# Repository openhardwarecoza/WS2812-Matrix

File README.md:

# WS2812-Matrix
LED Matrix Panels

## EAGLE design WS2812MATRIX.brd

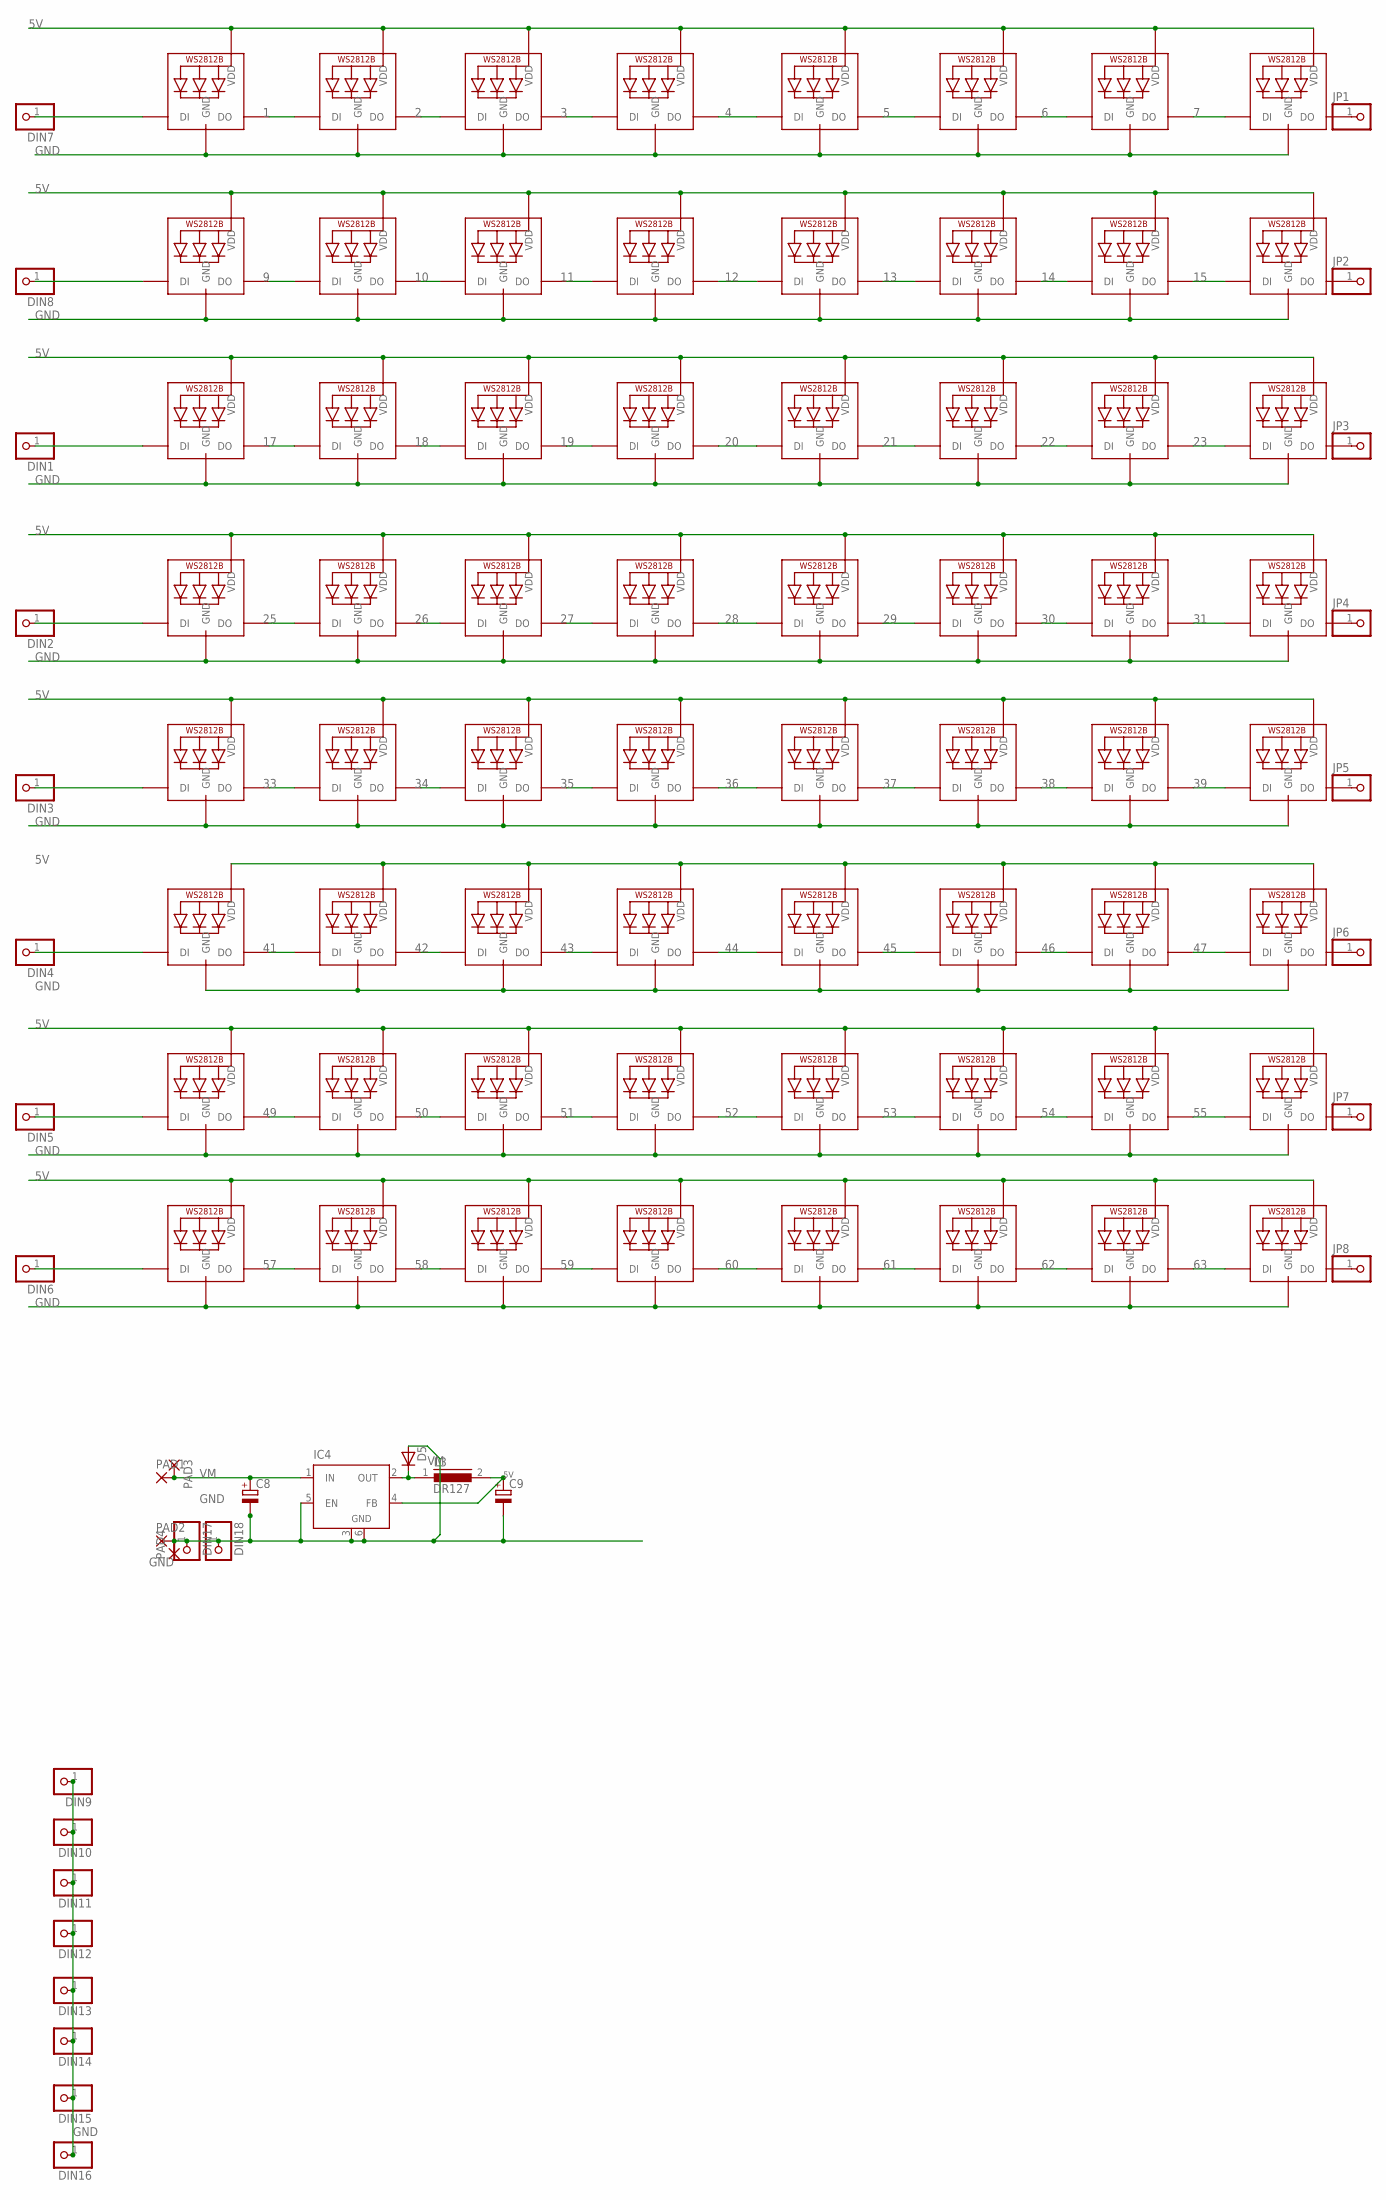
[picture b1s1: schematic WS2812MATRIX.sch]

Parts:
C8, C9: CPOL-EUE3.5-10; E3,5-10
D5: D-SOD-87; SOD87
DIN1, DIN2, DIN3, DIN4, DIN5, DIN6, DIN7, DIN8, DIN9, DIN10, DIN11, DIN12, DIN13, DIN14, DIN15, DIN16, DIN17, DIN18: PINHD-1X1; 1X01
IC4: LM2596S; TO263-5
JP1, JP2, JP3, JP4, JP5, JP6, JP7, JP8: PINHD-1X1; 1X01
L3: DR127
LED1, LED2, LED3, LED4, LED5, LED6, LED7, LED8, LED9, LED10, LED11, LED12, LED13, LED14, LED15, LED16, LED17, LED18, LED19, LED20, LED21, LED22, LED23, LED24, LED25, LED26, LED27, LED28, LED29, LED30, LED31, LED32, LED33, LED34, LED35, LED36, LED37, LED38, LED39, LED40, LED41, LED42, LED43, LED44, LED45, LED46, LED47, LED48, LED49, LED50, LED51, LED52, LED53, LED54, LED55, LED56, LED57, LED58, LED59, LED60, LED61, LED62, LED63, LED64: WS2812B5050; WS2812B
PAD1, PAD2, PAD3, PAD4: 2,54/1,1

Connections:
1: LED9.2-DOUT (DO), LED10.4-DIN (DI)
2: LED10.2-DOUT (DO), LED11.4-DIN (DI)
3: LED11.2-DOUT (DO), LED12.4-DIN (DI)
4: LED12.2-DOUT (DO), LED13.4-DIN (DI)
5: LED13.2-DOUT (DO), LED14.4-DIN (DI)
5V: C9.+, IC4.4 (FB), L3.2, LED1.1-VDD (VDD), LED2.1-VDD (VDD), LED3.1-VDD (VDD), LED4.1-VDD (VDD), LED5.1-VDD (VDD), LED6.1-VDD (VDD), LED7.1-VDD (VDD), LED8.1-VDD (VDD), LED9.1-VDD (VDD), LED10.1-VDD (VDD), LED11.1-VDD (VDD), LED12.1-VDD (VDD), LED13.1-VDD (VDD), LED14.1-VDD (VDD), LED15.1-VDD (VDD), LED16.1-VDD (VDD), LED17.1-VDD (VDD), LED18.1-VDD (VDD), LED19.1-VDD (VDD), LED20.1-VDD (VDD), LED21.1-VDD (VDD), LED22.1-VDD (VDD), LED23.1-VDD (VDD), LED24.1-VDD (VDD), LED25.1-VDD (VDD), LED26.1-VDD (VDD), LED27.1-VDD (VDD), LED28.1-VDD (VDD), LED29.1-VDD (VDD), LED30.1-VDD (VDD), LED31.1-VDD (VDD), LED32.1-VDD (VDD), LED33.1-VDD (VDD), LED34.1-VDD (VDD), LED35.1-VDD (VDD), LED36.1-VDD (VDD), LED37.1-VDD (VDD), LED38.1-VDD (VDD), LED39.1-VDD (VDD), LED40.1-VDD (VDD), LED41.1-VDD (VDD), LED42.1-VDD (VDD), LED43.1-VDD (VDD), LED44.1-VDD (VDD), LED45.1-VDD (VDD), LED46.1-VDD (VDD), LED47.1-VDD (VDD), LED48.1-VDD (VDD), LED49.1-VDD (VDD), LED50.1-VDD (VDD), LED51.1-VDD (VDD), LED52.1-VDD (VDD), LED53.1-VDD (VDD), LED54.1-VDD (VDD), LED55.1-VDD (VDD), LED56.1-VDD (VDD), LED57.1-VDD (VDD), LED58.1-VDD (VDD), LED59.1-VDD (VDD), LED60.1-VDD (VDD), LED61.1-VDD (VDD), LED62.1-VDD (VDD), LED63.1-VDD (VDD), LED64.1-VDD (VDD)
6: LED14.2-DOUT (DO), LED15.4-DIN (DI)
7: LED15.2-DOUT (DO), LED16.4-DIN (DI)
9: LED1.2-DOUT (DO), LED2.4-DIN (DI)
10: LED2.2-DOUT (DO), LED3.4-DIN (DI)
11: LED3.2-DOUT (DO), LED4.4-DIN (DI)
12: LED4.2-DOUT (DO), LED5.4-DIN (DI)
13: LED5.2-DOUT (DO), LED6.4-DIN (DI)
14: LED6.2-DOUT (DO), LED7.4-DIN (DI)
15: LED7.2-DOUT (DO), LED8.4-DIN (DI)
17: LED17.2-DOUT (DO), LED18.4-DIN (DI)
18: LED18.2-DOUT (DO), LED19.4-DIN (DI)
19: LED19.2-DOUT (DO), LED20.4-DIN (DI)
20: LED20.2-DOUT (DO), LED21.4-DIN (DI)
21: LED21.2-DOUT (DO), LED22.4-DIN (DI)
22: LED22.2-DOUT (DO), LED23.4-DIN (DI)
23: LED23.2-DOUT (DO), LED24.4-DIN (DI)
25: LED25.2-DOUT (DO), LED26.4-DIN (DI)
26: LED26.2-DOUT (DO), LED27.4-DIN (DI)
27: LED27.2-DOUT (DO), LED28.4-DIN (DI)
28: LED28.2-DOUT (DO), LED29.4-DIN (DI)
29: LED29.2-DOUT (DO), LED30.4-DIN (DI)
30: LED30.2-DOUT (DO), LED31.4-DIN (DI)
31: LED31.2-DOUT (DO), LED32.4-DIN (DI)
33: LED33.2-DOUT (DO), LED34.4-DIN (DI)
34: LED34.2-DOUT (DO), LED35.4-DIN (DI)
35: LED35.2-DOUT (DO), LED36.4-DIN (DI)
36: LED36.2-DOUT (DO), LED37.4-DIN (DI)
37: LED37.2-DOUT (DO), LED38.4-DIN (DI)
38: LED38.2-DOUT (DO), LED39.4-DIN (DI)
39: LED39.2-DOUT (DO), LED40.4-DIN (DI)
41: LED41.2-DOUT (DO), LED42.4-DIN (DI)
42: LED42.2-DOUT (DO), LED43.4-DIN (DI)
43: LED43.2-DOUT (DO), LED44.4-DIN (DI)
44: LED44.2-DOUT (DO), LED45.4-DIN (DI)
45: LED45.2-DOUT (DO), LED46.4-DIN (DI)
46: LED46.2-DOUT (DO), LED47.4-DIN (DI)
47: LED47.2-DOUT (DO), LED48.4-DIN (DI)
49: LED49.2-DOUT (DO), LED50.4-DIN (DI)
50: LED50.2-DOUT (DO), LED51.4-DIN (DI)
51: LED51.2-DOUT (DO), LED52.4-DIN (DI)
52: LED52.2-DOUT (DO), LED53.4-DIN (DI)
53: LED53.2-DOUT (DO), LED54.4-DIN (DI)
54: LED54.2-DOUT (DO), LED55.4-DIN (DI)
55: LED55.2-DOUT (DO), LED56.4-DIN (DI)
57: LED57.2-DOUT (DO), LED58.4-DIN (DI)
58: LED58.2-DOUT (DO), LED59.4-DIN (DI)
59: LED59.2-DOUT (DO), LED60.4-DIN (DI)
60: LED60.2-DOUT (DO), LED61.4-DIN (DI)
61: LED61.2-DOUT (DO), LED62.4-DIN (DI)
62: LED62.2-DOUT (DO), LED63.4-DIN (DI)
63: LED63.2-DOUT (DO), LED64.4-DIN (DI)
GND: C8.-, C9.-, D5.2 (A), DIN9.1, DIN10.1, DIN11.1, DIN12.1, DIN13.1, DIN14.1, DIN15.1, DIN16.1, DIN17.1, DIN18.1, IC4.3 (GND), IC4.5 (EN), IC4.6 (GND), LED1.3-GND (GND), LED2.3-GND (GND), LED3.3-GND (GND), LED4.3-GND (GND), LED5.3-GND (GND), LED6.3-GND (GND), LED7.3-GND (GND), LED8.3-GND (GND), LED9.3-GND (GND), LED10.3-GND (GND), LED11.3-GND (GND), LED12.3-GND (GND), LED13.3-GND (GND), LED14.3-GND (GND), LED15.3-GND (GND), LED16.3-GND (GND), LED17.3-GND (GND), LED18.3-GND (GND), LED19.3-GND (GND), LED20.3-GND (GND), LED21.3-GND (GND), LED22.3-GND (GND), LED23.3-GND (GND), LED24.3-GND (GND), LED25.3-GND (GND), LED26.3-GND (GND), LED27.3-GND (GND), LED28.3-GND (GND), LED29.3-GND (GND), LED30.3-GND (GND), LED31.3-GND (GND), LED32.3-GND (GND), LED33.3-GND (GND), LED34.3-GND (GND), LED35.3-GND (GND), LED36.3-GND (GND), LED37.3-GND (GND), LED38.3-GND (GND), LED39.3-GND (GND), LED40.3-GND (GND), LED41.3-GND (GND), LED42.3-GND (GND), LED43.3-GND (GND), LED44.3-GND (GND), LED45.3-GND (GND), LED46.3-GND (GND), LED47.3-GND (GND), LED48.3-GND (GND), LED49.3-GND (GND), LED50.3-GND (GND), LED51.3-GND (GND), LED52.3-GND (GND), LED53.3-GND (GND), LED54.3-GND (GND), LED55.3-GND (GND), LED56.3-GND (GND), LED57.3-GND (GND), LED58.3-GND (GND), LED59.3-GND (GND), LED60.3-GND (GND), LED61.3-GND (GND), LED62.3-GND (GND), LED63.3-GND (GND), LED64.3-GND (GND), PAD2.1, PAD4.1
unnamed: DIN7.1, LED9.4-DIN (DI)
unnamed: DIN1.1, LED17.4-DIN (DI)
unnamed: DIN2.1, LED25.4-DIN (DI)
unnamed: DIN3.1, LED33.4-DIN (DI)
unnamed: DIN4.1, LED41.4-DIN (DI)
unnamed: DIN5.1, LED49.4-DIN (DI)
unnamed: DIN6.1, LED57.4-DIN (DI)
unnamed: DIN8.1, LED1.4-DIN (DI)
unnamed: D5.1 (C), IC4.2 (OUT), L3.1
unnamed: JP1.1, LED16.2-DOUT (DO)
unnamed: JP2.1, LED8.2-DOUT (DO)
unnamed: JP3.1, LED24.2-DOUT (DO)
unnamed: JP4.1, LED32.2-DOUT (DO)
unnamed: JP5.1, LED40.2-DOUT (DO)
unnamed: JP6.1, LED48.2-DOUT (DO)
unnamed: JP7.1, LED56.2-DOUT (DO)
unnamed: JP8.1, LED64.2-DOUT (DO)
VM: C8.+, IC4.1 (IN), PAD1.1, PAD3.1

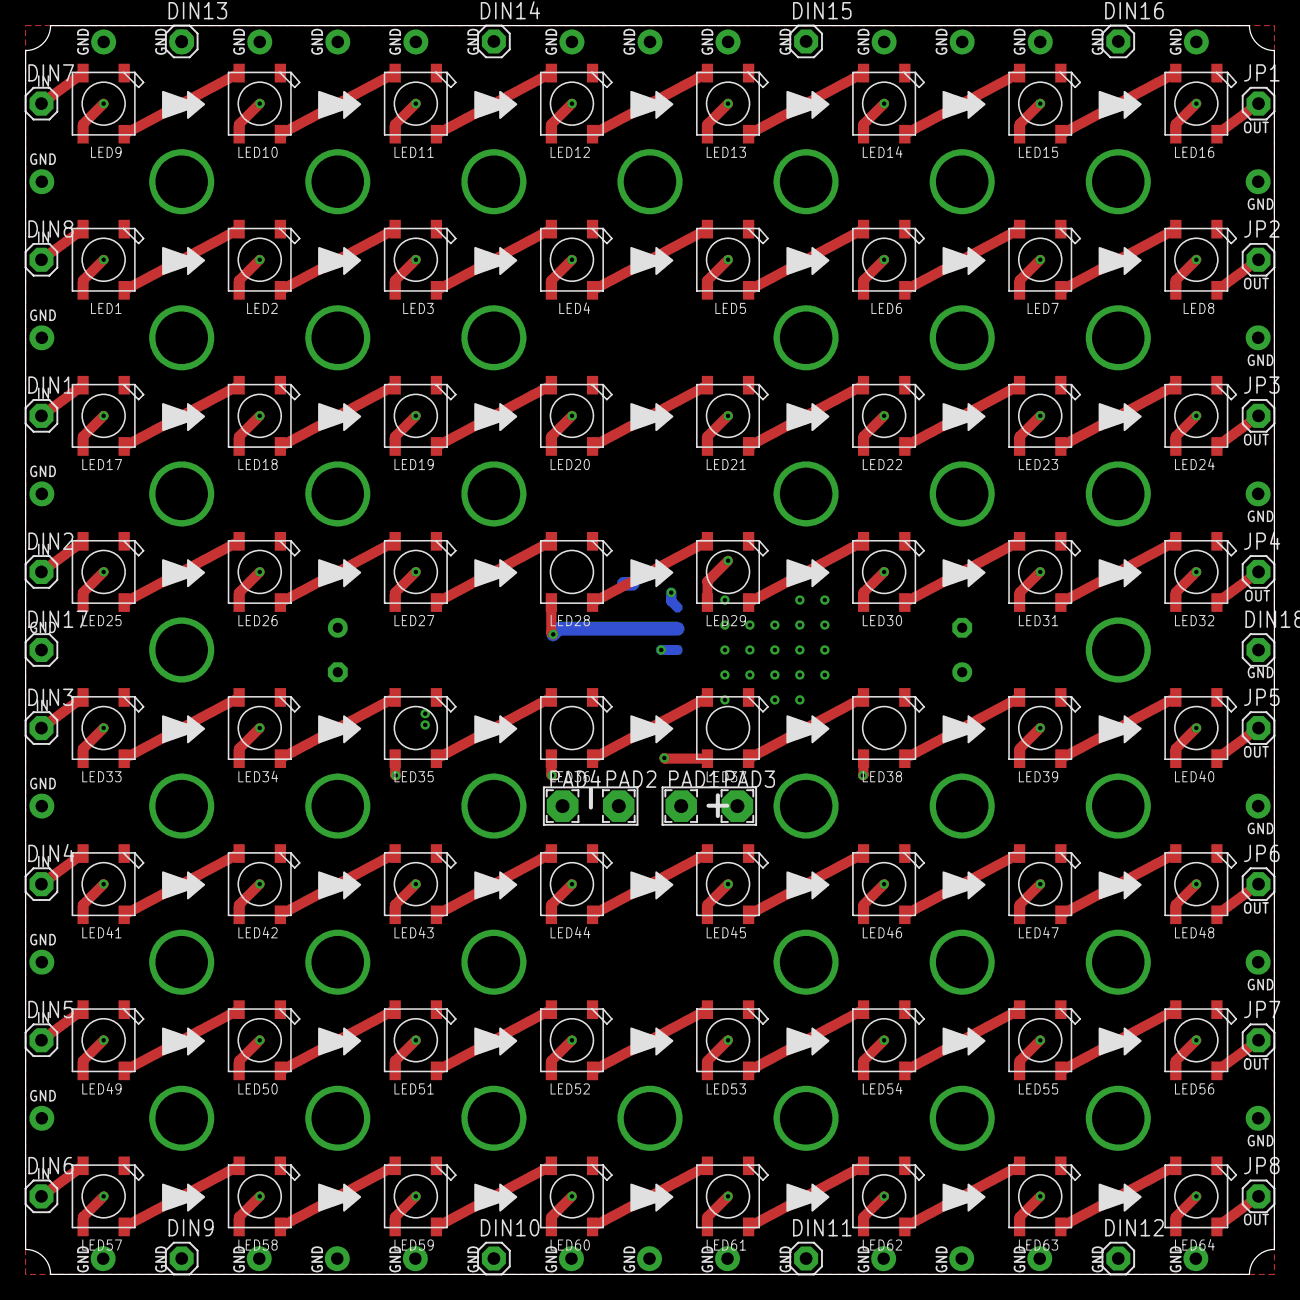
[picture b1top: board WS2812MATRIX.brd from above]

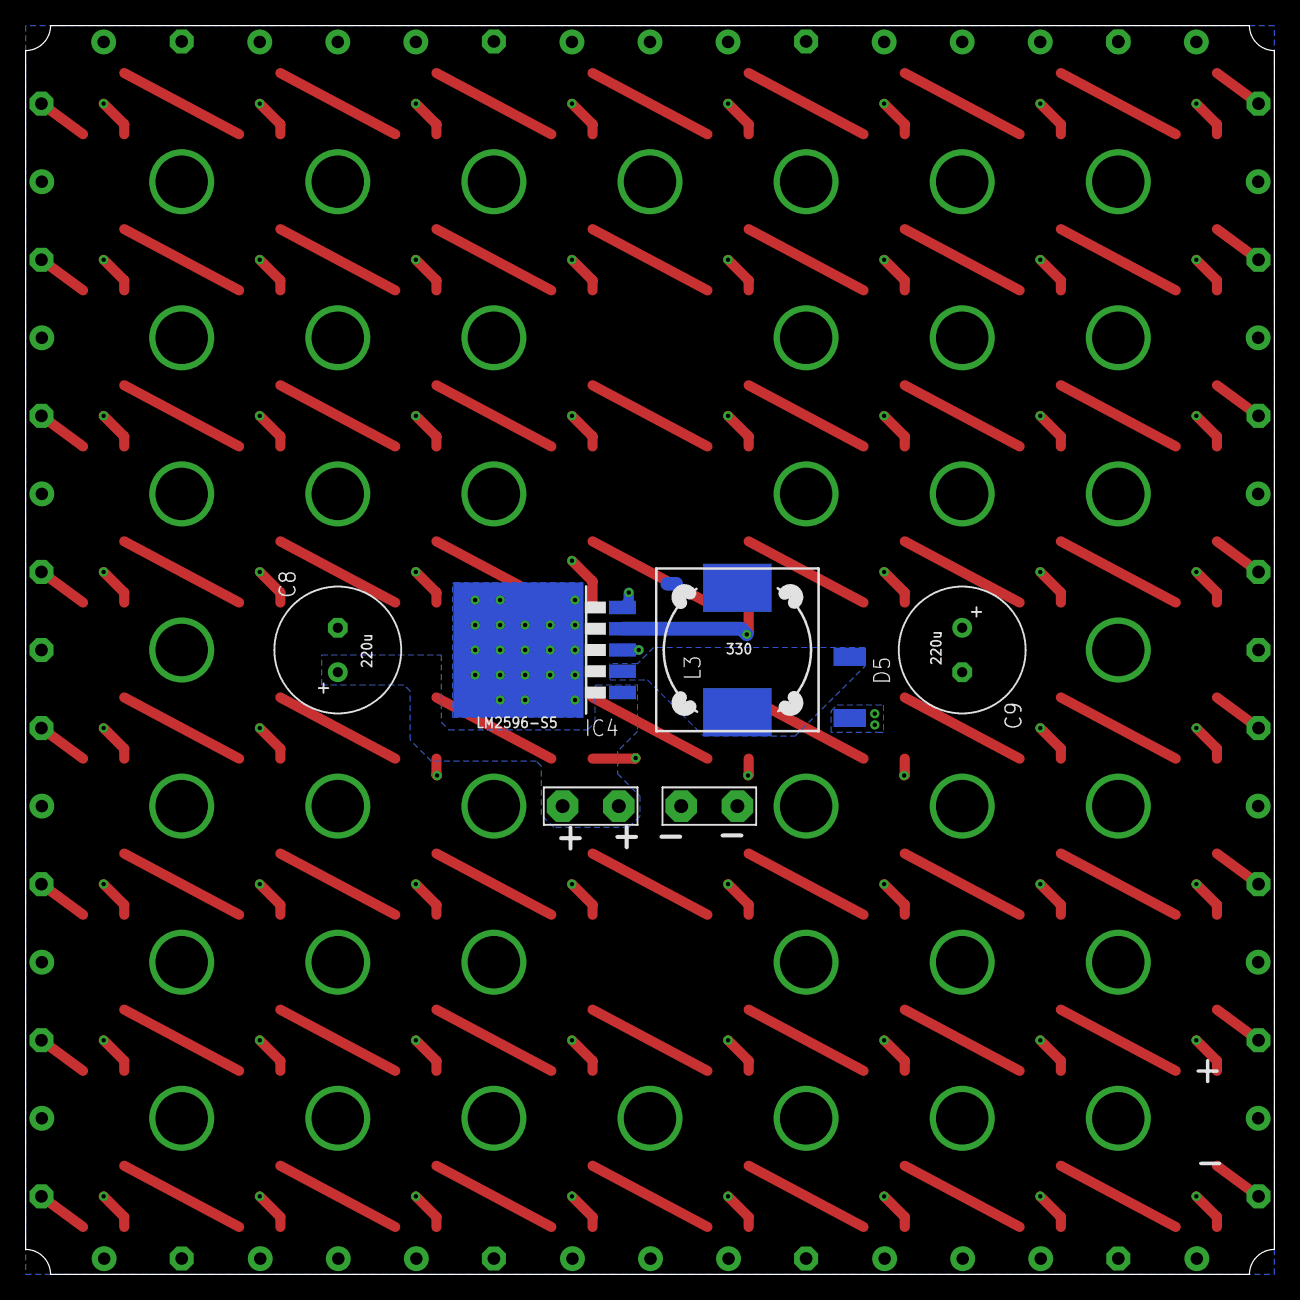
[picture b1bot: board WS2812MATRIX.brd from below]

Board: 2 copper layers, 100.0 x 100.0 mm, 99 parts (5 on the bottom side), 76 nets.

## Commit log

2018-10-23 archive
